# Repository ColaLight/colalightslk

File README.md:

COLALIGHTSLK
============

COLALIGHT SLK IS A LOW COST SOLAR LIGHTING KIT FOR RURAL FAMILIES IN THE THE DEVELOPING WORLD.

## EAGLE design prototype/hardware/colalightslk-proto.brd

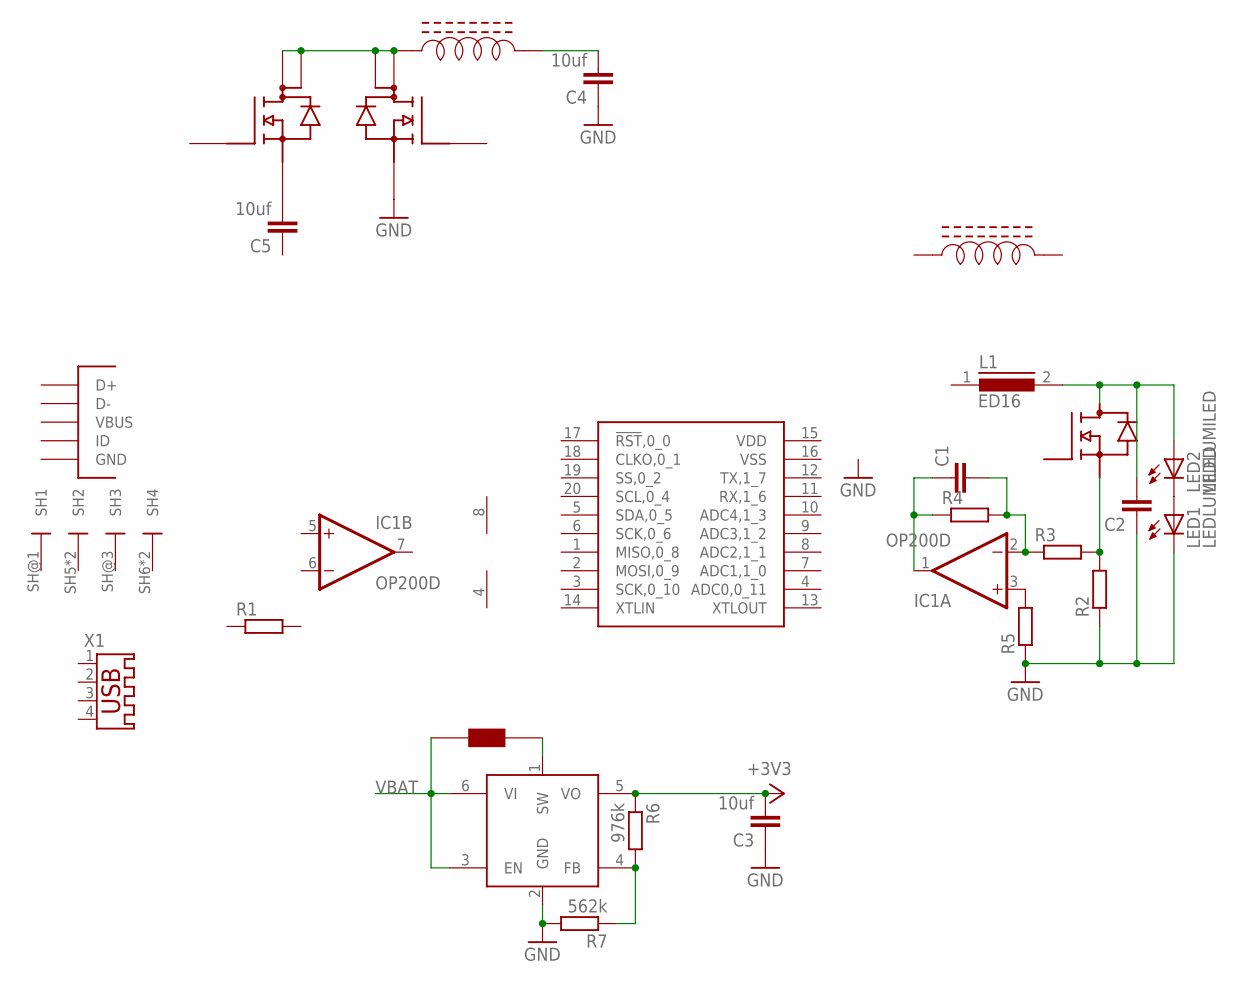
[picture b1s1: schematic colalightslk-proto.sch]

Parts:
C1, C2: C-EUC0805; C0805
C3, C4, C5: 10uf; C0805
IC1: OP200D; SO08
L1: ED16
LED1, LED2: LEDLUMILED; LUMILED
R1, R2: R-EU_R1210; R1210
R3, R4, R5: R-EU_R0805; R0805
R6: 976k; R0805
R7: 562k; R0805
U$1: LPC111XFD20; TSSOP-20
U$2: FCI-MICROUSB-B-PEG; MICROUSB-B-PEG
U$3: NTD4963N; IPAK
U$4: MCP1623/4; SOT23-6
U$5: 4.7uH; TAIYO-YUDEN-2016
U$6: NTMD4820NR2G; SOIC-8-NARROW
U$8, U$9: NRS6028; NRS60XX
X1: USB-A003

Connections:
+3V3: C3.2, R6.1, U$4.5 (VO)
GND: C2.1, C3.1, C4.1, LED1.4- (C), R2.1, R5.1, R7.2, U$4.2 (GND), U$6.3 (S2)
unnamed: LED1.2+ (A), LED2.4- (C)
unnamed: C2.2, L1.2, LED2.2+ (A), U$3.P$2 (D)
unnamed: R2.2, R3.2, U$3.P$3 (S)
unnamed: IC1.3 (+IN), R5.2
unnamed: R6.2, R7.1, U$4.4 (FB)
unnamed: C1.2, IC1.2 (-IN), R3.1, R4.2
unnamed: C1.1, IC1.1 (OUT), R4.1
unnamed: C4.2, U$9.P$2 (L2)
unnamed: U$4.1 (SW), U$5.P$2
unnamed: C5.2, U$6.1 (S1)
unnamed: U$6.5 (DP2), U$6.6 (D2), U$6.7 (DP1), U$6.8 (D1), U$9.P$1 (L1)
V+: IC1.8 (V+)
V-: IC1.4 (V-)
VBAT: U$4.3 (EN), U$4.6 (VI), U$5.P$1

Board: 2 copper layers, 25 parts (3 on the bottom side), 14 nets, no tracks yet.

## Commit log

2013-11-06 Added puntuation
2013-11-06 Added Requirements file
2013-11-06 Edited Specifications
2013-11-06 Added roles
2013-11-06 Added roles and moved requirements
2013-11-06 Formatted Roles
2013-11-06 Corrected spelling
2013-11-06 Improved formatting
2013-11-06 Minor refinement
2013-11-06 Added designer role
2013-11-06 added protection to specs and bonusses to roles
2013-11-08 Added basic proto board
2013-11-26 Added outline BOM
2013-11-26 Updated BOM, Solar Panel description
2013-11-26 Updated BOM , remaining descriptions
2013-11-26 Updated Roles
2013-11-26 Updated Roles, corrected role overlap
2013-11-29 Updated roles desireable to be none micro specific
2014-01-24 Added roadmap for comissioning support documentation
2014-01-24 Ficed a few typos
2014-03-07 Added first prototype design review
2014-03-07 corrected design review spelling
2014-03-07 corrected design review heading levels
2014-03-07 corrected design review added next aux features
2014-03-07 corrected design review corrected headings
2014-03-07 corrected design review corrected user op
